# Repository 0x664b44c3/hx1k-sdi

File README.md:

# HX1k-SDI
An SDI encoder/serializer on Lattice iCE40 FPGAs

The iCE40 series of FPGAs is low cost and is supported by an opensource toolchain (though not currently used for this project)
The devices are low density and low speed and lack advanced features like SerDes or true LVDS-IO, though.

## Features of the serializer
 * fits multiple times into an 1k gates iCE40 FPGA
 * fpga-vendor agnostic, besides the specific instantiation of the SB_IO for DDR out
 * needs one PLL running at half the bitrate (or at full bitrate if your IO can run at 270MHz)
 * should be extendable to generate DVB-ASI (would need 8B/10B instead of SMPTE scrambler and NRZI)
 * accepts bt.656 video at 27MHz word rate

## Abstract
This project implements an SD-SDI serializer (aka transmitter) completely in fabric, requiring nothing but an unused PLL
that is used to generate a 135MHz from an externally supplied 27MHz sample clock (27MWords/s with CbYCrY 4:2:2 encoding, 
13.5MHz pixel clock).
Most of the logic operates at 27MHz with just the final multiplexer and a DDR-out buffer running at the full 135MHz.

## Features of the test board
 * iCE40HX1k FPGA
 * 27MHz crystal oscillator
 * 10bit bt.656 video port
 * TVP5151 video decoder to test analog to sdi conversion
   * alternatively/additionally an LMH1881 can be fitted
 * 1MByte (512kx16) of SRAM taht can hold one complete frame of interlaced PAL/NTCS
 * ATSAMD21G18 MCU for programming the FPGA config flash and configuring the TVP, can be omitted
 * 4-pin header for I2C 128x32 OLED display
 * FPGA config pins on pinheader to allow flashing the config without a MCU
 * switchmode regulator for the 3.3V rail, allows input voltages of 5 to 12V
* Current functionality in the FPGA demo project
   * Color bars generator
   * SDI pathological pattern generator
   * Analog to SDI converter
   * About half the FPGA is still free for additional functionality

## Scope
This project contains a complete eval board for SDI video generation on
iCE40-HX FPGAs. UP-series might work, too, but it's unclear if the IOB and Fabric are fast enaugh
(might test it on iCEBreaker at some point in time).

## Contents
This project consists of the following subfolders:
 * fpga: the FPGA design (VHDL, iCECube2 project)
 * hardware: The board design (eagle 6), schematic diagrams as PDF
 * firmware: Firmware for the ATSAMD21 MCU that is on the board as well
 * release: synthesized FPGA config, firmware image, gerbers etc

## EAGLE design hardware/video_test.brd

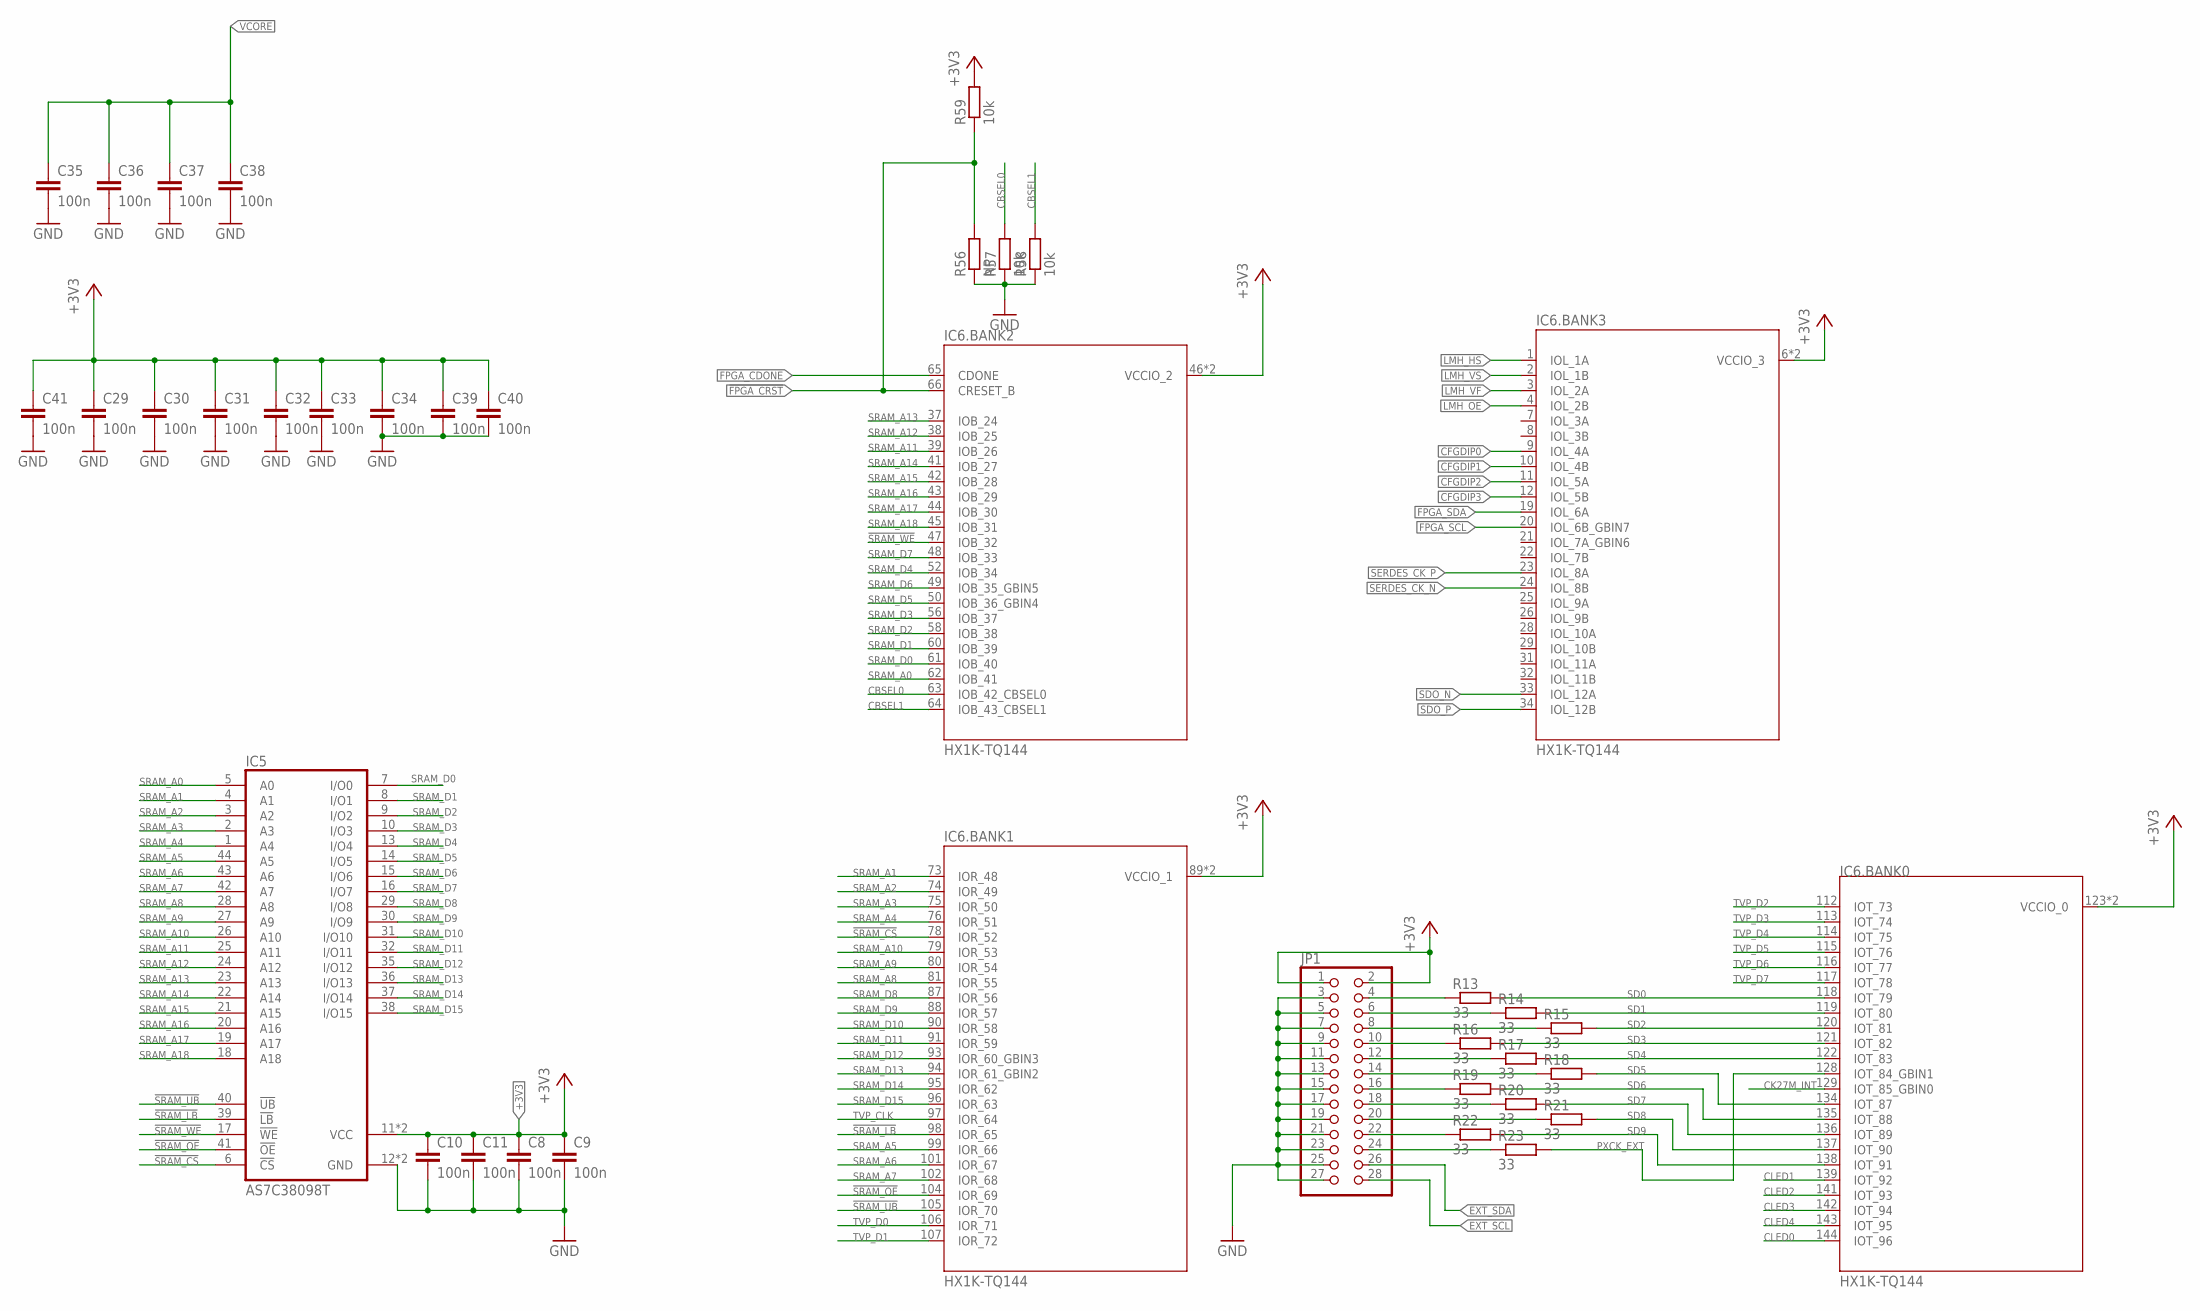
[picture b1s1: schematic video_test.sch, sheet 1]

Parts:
C8, C9: 100n; C0603
C10, C11, C29, C30, C31, C32, C33, C34, C35, C36, C37, C38, C39, C40, C41: 100n; C0402
IC5: AS7C38098T; TSOPII-Z44
IC6: HX1K-TQ144; QFP50P2200X2200X160-144N
JP1: PINHD-2X14; 2X14
R13, R14, R15, R16, R17, R18, R19, R20, R21, R22, R23: 33; R0603
R56: NP; R0402
R57, R58, R59: 10k; R0402

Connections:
!FPGA_CRST!: IC6.66 (CRESET_B), R56.2, R59.1; also elsewhere on the board
!SRAM_CS!: IC5.6 (!CS!), IC6.78 (IOR_52)
!SRAM_LB!: IC5.39 (!LB!), IC6.98 (IOR_65)
!SRAM_OE!: IC5.41 (!OE!), IC6.104 (IOR_69)
!SRAM_UB!: IC5.40 (!UB!), IC6.105 (IOR_70)
!SRAM_WE!: IC5.17 (!WE!), IC6.47 (IOB_32)
+3V3: C8.1, C9.1, C10.1, C11.1, C29.1, C30.1, C31.1, C32.1, C33.1, C34.1, C39.1, C40.1, C41.1, IC5.11 (VCC), IC5.33 (VCC), IC6.6 (VCCIO_3), IC6.30 (VCCIO_3), IC6.46 (VCCIO_2), IC6.57 (VCCIO_2), IC6.89 (VCCIO_1), IC6.100 (VCCIO_1), IC6.123 (VCCIO_0), IC6.133 (VCCIO_0), JP1.1, JP1.2, R59.2; also elsewhere on the board
CBSEL0: IC6.63 (IOB_42_CBSEL0), R57.2; also elsewhere on the board
CBSEL1: IC6.64 (IOB_43_CBSEL1), R58.2; also elsewhere on the board
CFGDIP0: IC6.9 (IOL_4A); also elsewhere on the board
CFGDIP1: IC6.10 (IOL_4B); also elsewhere on the board
CFGDIP2: IC6.11 (IOL_5A); also elsewhere on the board
CFGDIP3: IC6.12 (IOL_5B); also elsewhere on the board
CK27M_INT: IC6.129 (IOT_85_GBIN0); also elsewhere on the board
CLED0: IC6.144 (IOT_96); also elsewhere on the board
CLED1: IC6.139 (IOT_92); also elsewhere on the board
CLED2: IC6.141 (IOT_93); also elsewhere on the board
CLED3: IC6.142 (IOT_94); also elsewhere on the board
CLED4: IC6.143 (IOT_95); also elsewhere on the board
EXT_SCL: JP1.28; also elsewhere on the board
EXT_SDA: JP1.26; also elsewhere on the board
FPGA_CDONE: IC6.65 (CDONE); also elsewhere on the board
FPGA_SCL: IC6.20 (IOL_6B_GBIN7); also elsewhere on the board
FPGA_SDA: IC6.19 (IOL_6A); also elsewhere on the board
GND: C8.2, C9.2, C10.2, C11.2, C29.2, C30.2, C31.2, C32.2, C33.2, C34.2, C35.2, C36.2, C37.2, C38.2, C39.2, C40.2, C41.2, IC5.12 (GND), IC5.34 (GND), JP1.3, JP1.5, JP1.7, JP1.9, JP1.11, JP1.13, JP1.15, JP1.17, JP1.19, JP1.21, JP1.23, JP1.25, JP1.27, R56.1, R57.1, R58.1; also elsewhere on the board
LMH_HS: IC6.1 (IOL_1A); also elsewhere on the board
LMH_OE: IC6.4 (IOL_2B); also elsewhere on the board
LMH_VF: IC6.3 (IOL_2A); also elsewhere on the board
LMH_VS: IC6.2 (IOL_1B); also elsewhere on the board
unnamed: JP1.4, R13.1
unnamed: JP1.6, R14.1
unnamed: JP1.8, R15.1
unnamed: JP1.10, R16.1
unnamed: JP1.12, R17.1
unnamed: JP1.14, R18.1
unnamed: JP1.16, R19.1
unnamed: JP1.18, R20.1
unnamed: JP1.20, R21.1
unnamed: JP1.22, R22.1
unnamed: JP1.24, R23.1
PXCK_EXT: IC6.128 (IOT_84_GBIN1), R23.2
SD0: IC6.118 (IOT_79), R13.2
SD1: IC6.119 (IOT_80), R14.2
SD2: IC6.120 (IOT_81), R15.2
SD3: IC6.121 (IOT_82), R16.2
SD4: IC6.122 (IOT_83), R17.2
SD5: IC6.134 (IOT_87), R18.2
SD6: IC6.135 (IOT_88), R19.2
SD7: IC6.136 (IOT_89), R20.2
SD8: IC6.137 (IOT_90), R21.2
SD9: IC6.138 (IOT_91), R22.2
SDO_N: IC6.33 (IOL_12A); also elsewhere on the board
SDO_P: IC6.34 (IOL_12B); also elsewhere on the board
SERDES_CK_N: IC6.24 (IOL_8B); also elsewhere on the board
SERDES_CK_P: IC6.23 (IOL_8A); also elsewhere on the board
SRAM_A0: IC5.5 (A0), IC6.62 (IOB_41)
SRAM_A1: IC5.4 (A1), IC6.73 (IOR_48)
SRAM_A2: IC5.3 (A2), IC6.74 (IOR_49)
SRAM_A3: IC5.2 (A3), IC6.75 (IOR_50)
SRAM_A4: IC5.1 (A4), IC6.76 (IOR_51)
SRAM_A5: IC5.44 (A5), IC6.99 (IOR_66)
SRAM_A6: IC5.43 (A6), IC6.101 (IOR_67)
SRAM_A7: IC5.42 (A7), IC6.102 (IOR_68)
SRAM_A8: IC5.28 (A8), IC6.81 (IOR_55)
SRAM_A9: IC5.27 (A9), IC6.80 (IOR_54)
SRAM_A10: IC5.26 (A10), IC6.79 (IOR_53)
SRAM_A11: IC5.25 (A11), IC6.39 (IOB_26)
SRAM_A12: IC5.24 (A12), IC6.38 (IOB_25)
SRAM_A13: IC5.23 (A13), IC6.37 (IOB_24)
SRAM_A14: IC5.22 (A14), IC6.41 (IOB_27)
SRAM_A15: IC5.21 (A15), IC6.42 (IOB_28)
SRAM_A16: IC5.20 (A16), IC6.43 (IOB_29)
SRAM_A17: IC5.19 (A17), IC6.44 (IOB_30)
SRAM_A18: IC5.18 (A18), IC6.45 (IOB_31)
SRAM_D0: IC5.7 (I/O0), IC6.61 (IOB_40)
SRAM_D1: IC5.8 (I/O1), IC6.60 (IOB_39)
SRAM_D2: IC5.9 (I/O2), IC6.58 (IOB_38)
SRAM_D3: IC5.10 (I/O3), IC6.56 (IOB_37)
SRAM_D4: IC5.13 (I/O4), IC6.52 (IOB_34)
SRAM_D5: IC5.14 (I/O5), IC6.50 (IOB_36_GBIN4)
SRAM_D6: IC5.15 (I/O6), IC6.49 (IOB_35_GBIN5)
SRAM_D7: IC5.16 (I/O7), IC6.48 (IOB_33)
SRAM_D8: IC5.29 (I/O8), IC6.87 (IOR_56)
SRAM_D9: IC5.30 (I/O9), IC6.88 (IOR_57)
SRAM_D10: IC5.31 (I/O10), IC6.90 (IOR_58)
SRAM_D11: IC5.32 (I/O11), IC6.91 (IOR_59)
SRAM_D12: IC5.35 (I/O12), IC6.93 (IOR_60_GBIN3)
SRAM_D13: IC5.36 (I/O13), IC6.94 (IOR_61_GBIN2)
SRAM_D14: IC5.37 (I/O14), IC6.95 (IOR_62)
SRAM_D15: IC5.38 (I/O15), IC6.96 (IOR_63)
TVP_CLK: IC6.97 (IOR_64); also elsewhere on the board
TVP_D0: IC6.106 (IOR_71); also elsewhere on the board
TVP_D1: IC6.107 (IOR_72); also elsewhere on the board
TVP_D2: IC6.112 (IOT_73); also elsewhere on the board
TVP_D3: IC6.113 (IOT_74); also elsewhere on the board
TVP_D4: IC6.114 (IOT_75); also elsewhere on the board
TVP_D5: IC6.115 (IOT_76); also elsewhere on the board
TVP_D6: IC6.116 (IOT_77); also elsewhere on the board
TVP_D7: IC6.117 (IOT_78); also elsewhere on the board
VCORE: C35.1, C36.1, C37.1, C38.1; also elsewhere on the board
VPP_FAST: IC6.109 (VPP_FAST)

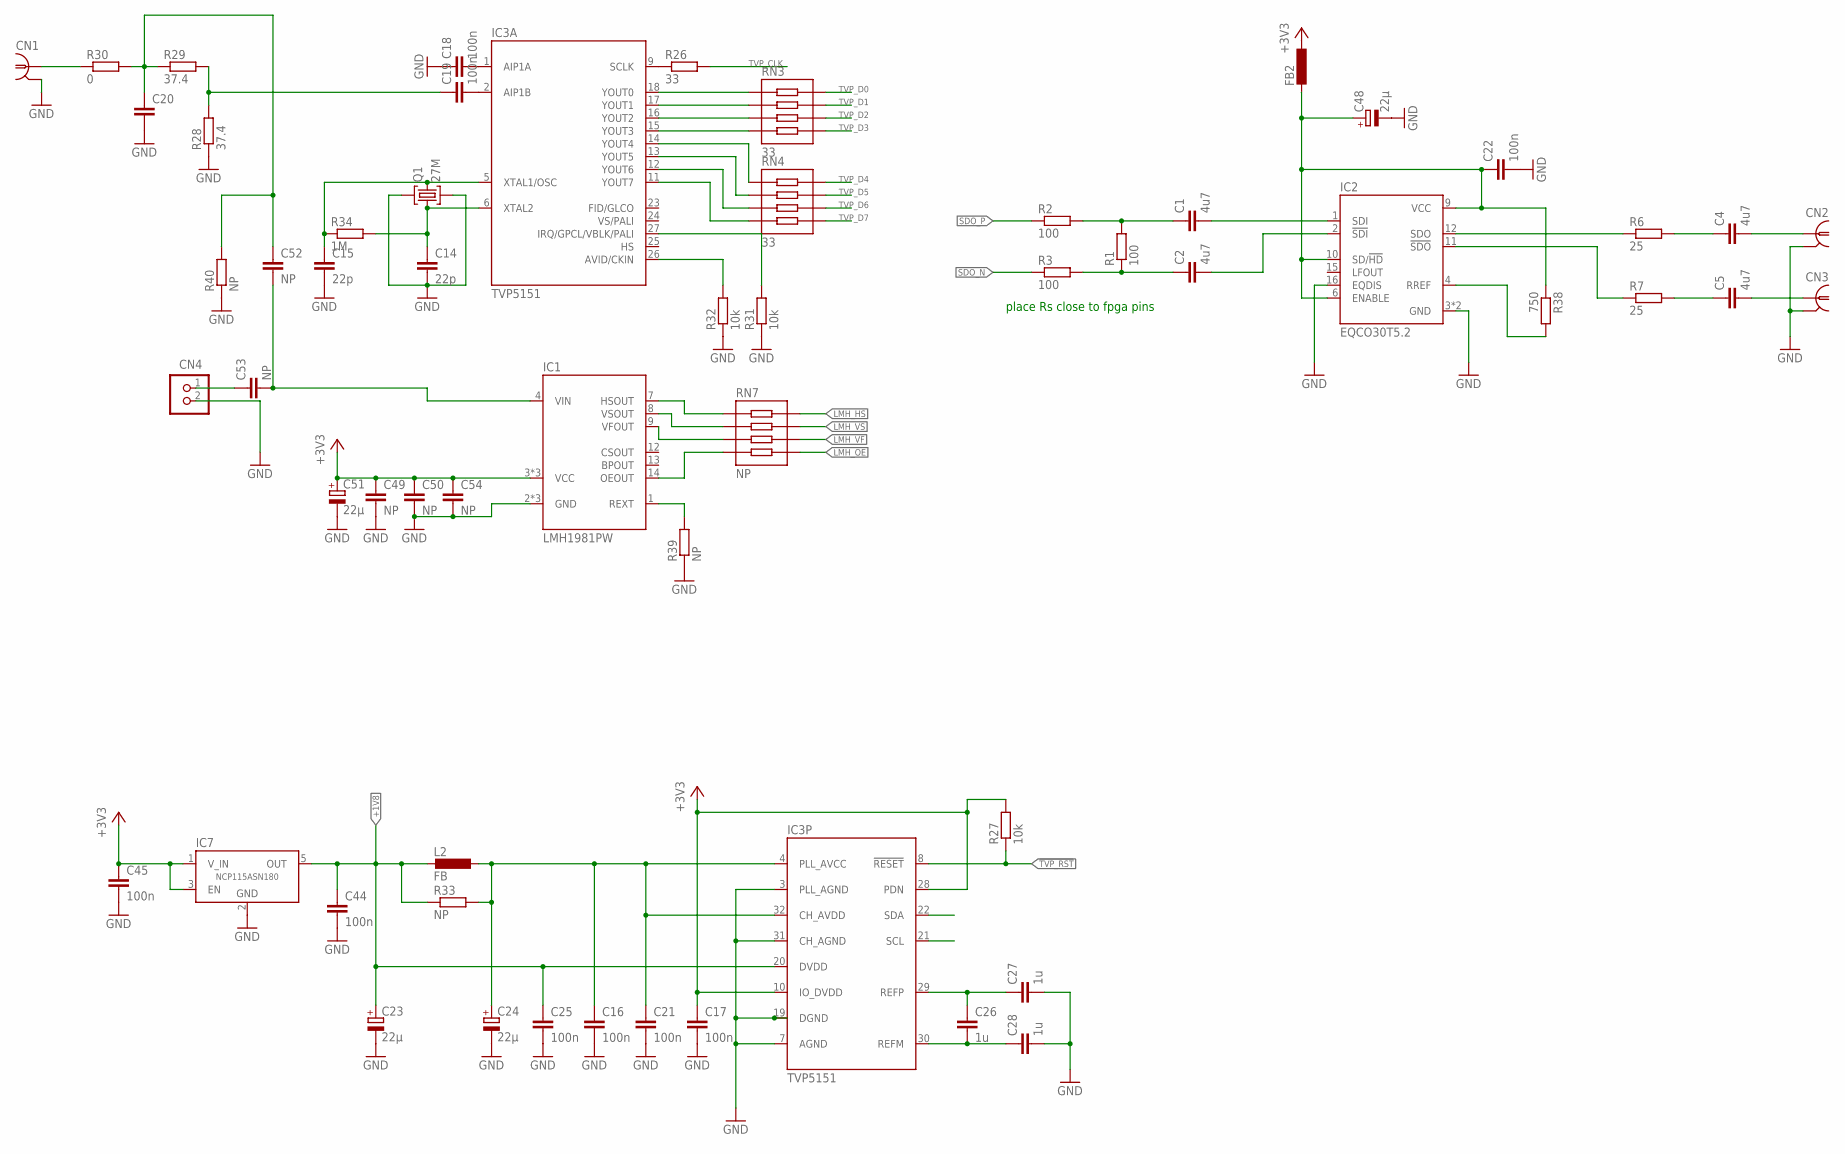
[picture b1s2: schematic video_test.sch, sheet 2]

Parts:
C1, C2, C4, C5: 4u7; C0603
C14, C15: 22p; C0603
C16, C17, C18, C19, C21, C22, C25: 100n; C0402
C20: C-EUC0603; C0603
C23, C24: 22µ; B/3528-21R
C26, C27, C28: 1u; C0603
C44, C45: 100n; C0603
C48, C51: 22µ; PANASONIC_B
C49, C50, C54: NP; C0402
C52, C53: NP; C0603
CN1, CN2, CN3: BU-BNC-RA; AMP_227161
CN4: JST-XH2; B2B-XH
FB2: L-EU_L0603; R0603
IC1: LMH1981PW; TSSOP14
IC2: EQCO30T5.2; QFN16_065
IC3: TVP5151; SPQFP32
IC7: NCP115ASN180; SOT23-5
L2: FB; R0805
Q1: 27M; MT
R1, R2, R3: 100; R0603
R6, R7: 25; R0603
R26: 33; R0603
R27, R31, R32: 10k; R0402
R28, R29: 37.4; R0603
R30: 0; R0603
R33, R39, R40: NP; R0603
R34: 1M; R0603
R38: 750; R0603
RN3, RN4: 33; CTS742C083
RN7: NP; CTS742C083

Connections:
!TVP_RST!: IC3.8 (!RESET!), R27.1
+1V8: C23.+, C25.1, C44.1, IC3.20 (DVDD), IC7.5 (OUT), L2.2, R33.1
+1V8_A: C16.1, C21.1, C24.+, IC3.4 (PLL_AVCC), IC3.32 (CH_AVDD), L2.1, R33.2
+3V3: C17.1, C45.1, C49.1, C50.1, C51.+, C54.1, FB2.1, IC1.3 (VCC), IC1.6 (VCC), IC1.11 (VCC), IC3.10 (IO_DVDD), IC3.28 (PDN), IC7.1 (V_IN), IC7.3 (EN), R27.2; also elsewhere on the board
GND: C14.2, C15.2, C16.2, C17.2, C18.1, C20.2, C21.2, C22.2, C23.-, C24.-, C25.2, C27.2, C28.2, C44.2, C45.2, C48.-, C49.2, C50.2, C51.-, C54.2, CN1.2 (GND), CN2.2 (GND), CN3.2 (GND), CN4.2, IC1.2 (GND), IC1.5 (GND), IC1.10 (GND), IC2.3 (GND), IC2.16 (EQDIS), IC2.TP (GND), IC3.3 (PLL_AGND), IC3.7 (AGND), IC3.19 (DGND), IC3.31 (CH_AGND), IC7.2 (GND), Q1.2 (G1), Q1.4 (G2), R28.1, R31.1, R32.1, R39.1, R40.1; also elsewhere on the board
LMH_HS: RN7.8 (B1); also elsewhere on the board
LMH_OE: RN7.5 (B4); also elsewhere on the board
LMH_VF: RN7.6 (B3); also elsewhere on the board
LMH_VS: RN7.7 (B2); also elsewhere on the board
unnamed: C1.2, IC2.1 (SDI)
unnamed: C2.2, IC2.2 (!SDI!)
unnamed: C2.1, R1.1, R3.2
unnamed: C1.1, R1.2, R2.2
unnamed: C4.1, R6.2
unnamed: C5.1, R7.2
unnamed: C4.2, CN2.1
unnamed: C5.2, CN3.1
unnamed: C22.1, C48.+, FB2.2, IC2.6 (ENABLE), IC2.9 (VCC), IC2.10 (SD/!HD!), R38.1
unnamed: IC2.4 (RREF), R38.2
unnamed: C15.1, IC3.5 (XTAL1/OSC), Q1.3 (2), R34.1
unnamed: C14.1, IC3.6 (XTAL2), Q1.1, R34.2
unnamed: C26.1, C27.1, IC3.29 (REFP)
unnamed: C26.2, C28.1, IC3.30 (REFM)
unnamed: C18.2, IC3.1 (AIP1A)
unnamed: IC3.11 (YOUT7), RN4.4 (A4)
unnamed: IC1.7 (HSOUT), RN7.1 (A1)
unnamed: IC3.9 (SCLK), R26.1
unnamed: IC3.12 (YOUT6), RN4.3 (A3)
unnamed: IC3.13 (YOUT5), RN4.2 (A2)
unnamed: IC3.14 (YOUT4), RN4.1 (A1)
unnamed: IC3.15 (YOUT3), RN3.4 (A4)
unnamed: IC3.16 (YOUT2), RN3.3 (A3)
unnamed: IC3.17 (YOUT1), RN3.2 (A2)
unnamed: IC3.18 (YOUT0), RN3.1 (A1)
unnamed: C19.2, IC3.2 (AIP1B)
unnamed: IC3.27 (IRQ/GPCL/VBLK/PALI), R31.2
unnamed: C19.1, R28.2, R29.2
unnamed: C20.1, C52.1, R29.1, R30.2, R40.2
unnamed: CN1.1, R30.1
unnamed: IC3.26 (AVID/CKIN), R32.2
unnamed: C52.2, C53.2, IC1.4 (VIN)
unnamed: C53.1, CN4.1
unnamed: IC1.8 (VSOUT), RN7.2 (A2)
unnamed: IC1.1 (REXT), R39.2
unnamed: IC1.9 (VFOUT), RN7.3 (A3)
unnamed: IC1.14 (OEOUT), RN7.4 (A4)
SCL: IC3.21 (SCL); also elsewhere on the board
SDA: IC3.22 (SDA); also elsewhere on the board
SDI_OUT_N: IC2.11 (!SDO!), R7.1
SDI_OUT_P: IC2.12 (SDO), R6.1
SDO_N: R3.1; also elsewhere on the board
SDO_P: R2.1; also elsewhere on the board
TVP_CLK: R26.2; also elsewhere on the board
TVP_D0: RN3.8 (B1); also elsewhere on the board
TVP_D1: RN3.7 (B2); also elsewhere on the board
TVP_D2: RN3.6 (B3); also elsewhere on the board
TVP_D3: RN3.5 (B4); also elsewhere on the board
TVP_D4: RN4.8 (B1); also elsewhere on the board
TVP_D5: RN4.7 (B2); also elsewhere on the board
TVP_D6: RN4.6 (B3); also elsewhere on the board
TVP_D7: RN4.5 (B4); also elsewhere on the board

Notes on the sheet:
place Rs close to fpga pins

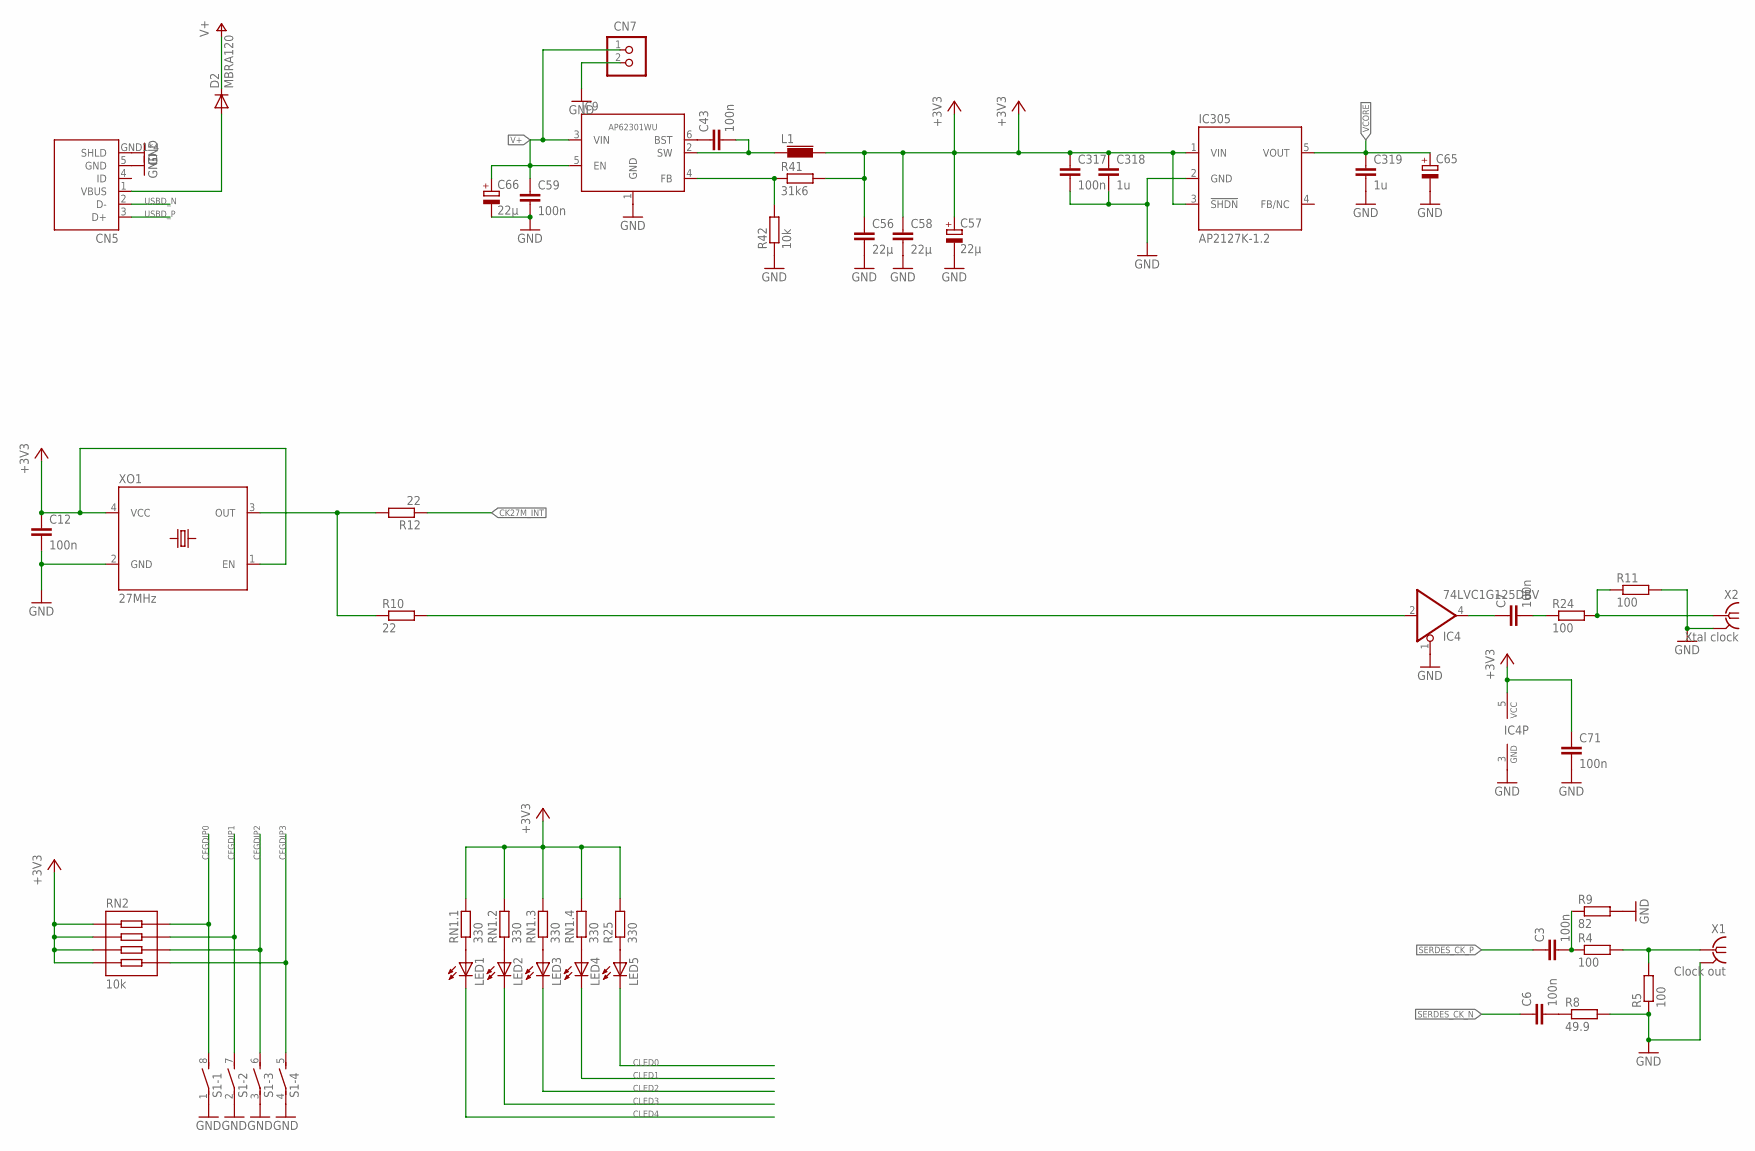
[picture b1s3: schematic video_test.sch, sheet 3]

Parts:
C3, C6, C7, C12, C43, C59, C71, C317: 100n; C0603
C56, C58: 22µ; C0805
C57: 22µ; PANASONIC_B
C65: CPOL-EUB/3528-21R; B/3528-21R
C66: 22µ; PANASONIC_C
C318, C319: 1u; C0603
CN5: USB-UJ2-MIBH-G; UJ2-MIBH-G-SMT
CN7: JST-XH2; B2B-XH
D2: MBRA120; SMA
IC4: 74LVC1G125DBV; SOT23-5
IC9: AP62301WU; SOT23-6L
IC305: AP2127K-1.2; SOT23-5
L1: L-TYA4020; TYA4020
LED1, LED2, LED3, LED4, LED5: LEDCHIP-LED0603; CHIP-LED0603
R4, R5, R11, R24: 100; R0603
R8: 49.9; R0603
R9: 82; R0603
R10, R12: 22; R0603
R25: 330; R0603
R41: 31k6; R0603
R42: 10k; R0603
RN1: 330; CTS742C083
RN2: 10k; CTS742C083
S1: DIP04S
X1: Clock out; BU-SMA-V
X2: Xtal clock; BU-SMA-V
XO1: 27MHz; ECS-2333

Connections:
+3V3: C12.1, C56.1, C57.+, C58.1, C71.1, C317.1, C318.1, IC4.5 (VCC), IC305.1 (VIN), IC305.3 (!SHDN!), L1.2, R25.2, R41.2, RN1.5 (2), RN1.6 (2), RN1.7 (2), RN1.8 (2), RN2.1 (A1), RN2.2 (A2), RN2.3 (A3), RN2.4 (A4), XO1.1 (EN), XO1.4 (VCC); also elsewhere on the board
CFGDIP0: RN2.8 (B1), S1.8 (2); also elsewhere on the board
CFGDIP1: RN2.7 (B2), S1.7 (2); also elsewhere on the board
CFGDIP2: RN2.6 (B3), S1.6 (2); also elsewhere on the board
CFGDIP3: RN2.5 (B4), S1.5 (2); also elsewhere on the board
CK27M_INT: R12.1; also elsewhere on the board
CLED0: LED5.C; also elsewhere on the board
CLED1: LED4.C; also elsewhere on the board
CLED2: LED3.C; also elsewhere on the board
CLED3: LED2.C; also elsewhere on the board
CLED4: LED1.C; also elsewhere on the board
GND: C12.2, C56.2, C57.-, C58.2, C59.2, C65.-, C66.-, C71.2, C317.2, C318.2, C319.2, CN5.5 (GND), CN5.GND1 (SHLD), CN5.GND2 (SHLD), CN5.GND3 (SHLD), CN5.GND4 (SHLD), CN7.2, IC4.1 (OE), IC4.3 (GND), IC9.1 (GND), IC305.2 (GND), R5.1, R8.2, R9.2, R11.2, R42.1, S1.1, S1.2 (1), S1.3 (1), S1.4 (1), X1.2 (GND), X1.3 (GND), X1.4 (GND), X1.5 (GND), X2.2 (GND), X2.3 (GND), X2.4 (GND), X2.5 (GND), XO1.2 (GND); also elsewhere on the board
unnamed: R4.2, R5.2, X1.1
unnamed: C6.2, R8.1
unnamed: C3.2, R4.1, R9.1
unnamed: R11.1, R24.2, X2.1
unnamed: IC4.2 (I), R10.2
unnamed: R10.1, R12.2, XO1.3 (OUT)
unnamed: C7.1, IC4.4 (O)
unnamed: C7.2, R24.1
unnamed: C43.2, IC9.2 (SW), L1.1
unnamed: LED1.A, RN1.1
unnamed: LED2.A, RN1.2 (1)
unnamed: LED3.A, RN1.3 (1)
unnamed: LED4.A, RN1.4 (1)
unnamed: LED5.A, R25.1
unnamed: C43.1, IC9.6 (BST)
unnamed: IC9.4 (FB), R41.1, R42.2
unnamed: CN5.1 (VBUS), D2.A
SERDES_CK_N: C6.1; also elsewhere on the board
SERDES_CK_P: C3.1; also elsewhere on the board
USBD_N: CN5.2 (D-); also elsewhere on the board
USBD_P: CN5.3 (D+); also elsewhere on the board
V+: C59.1, C66.+, CN7.1, D2.C, IC9.3 (VIN), IC9.5 (EN)
VCORE: C65.+, C319.1, IC305.5 (VOUT); also elsewhere on the board

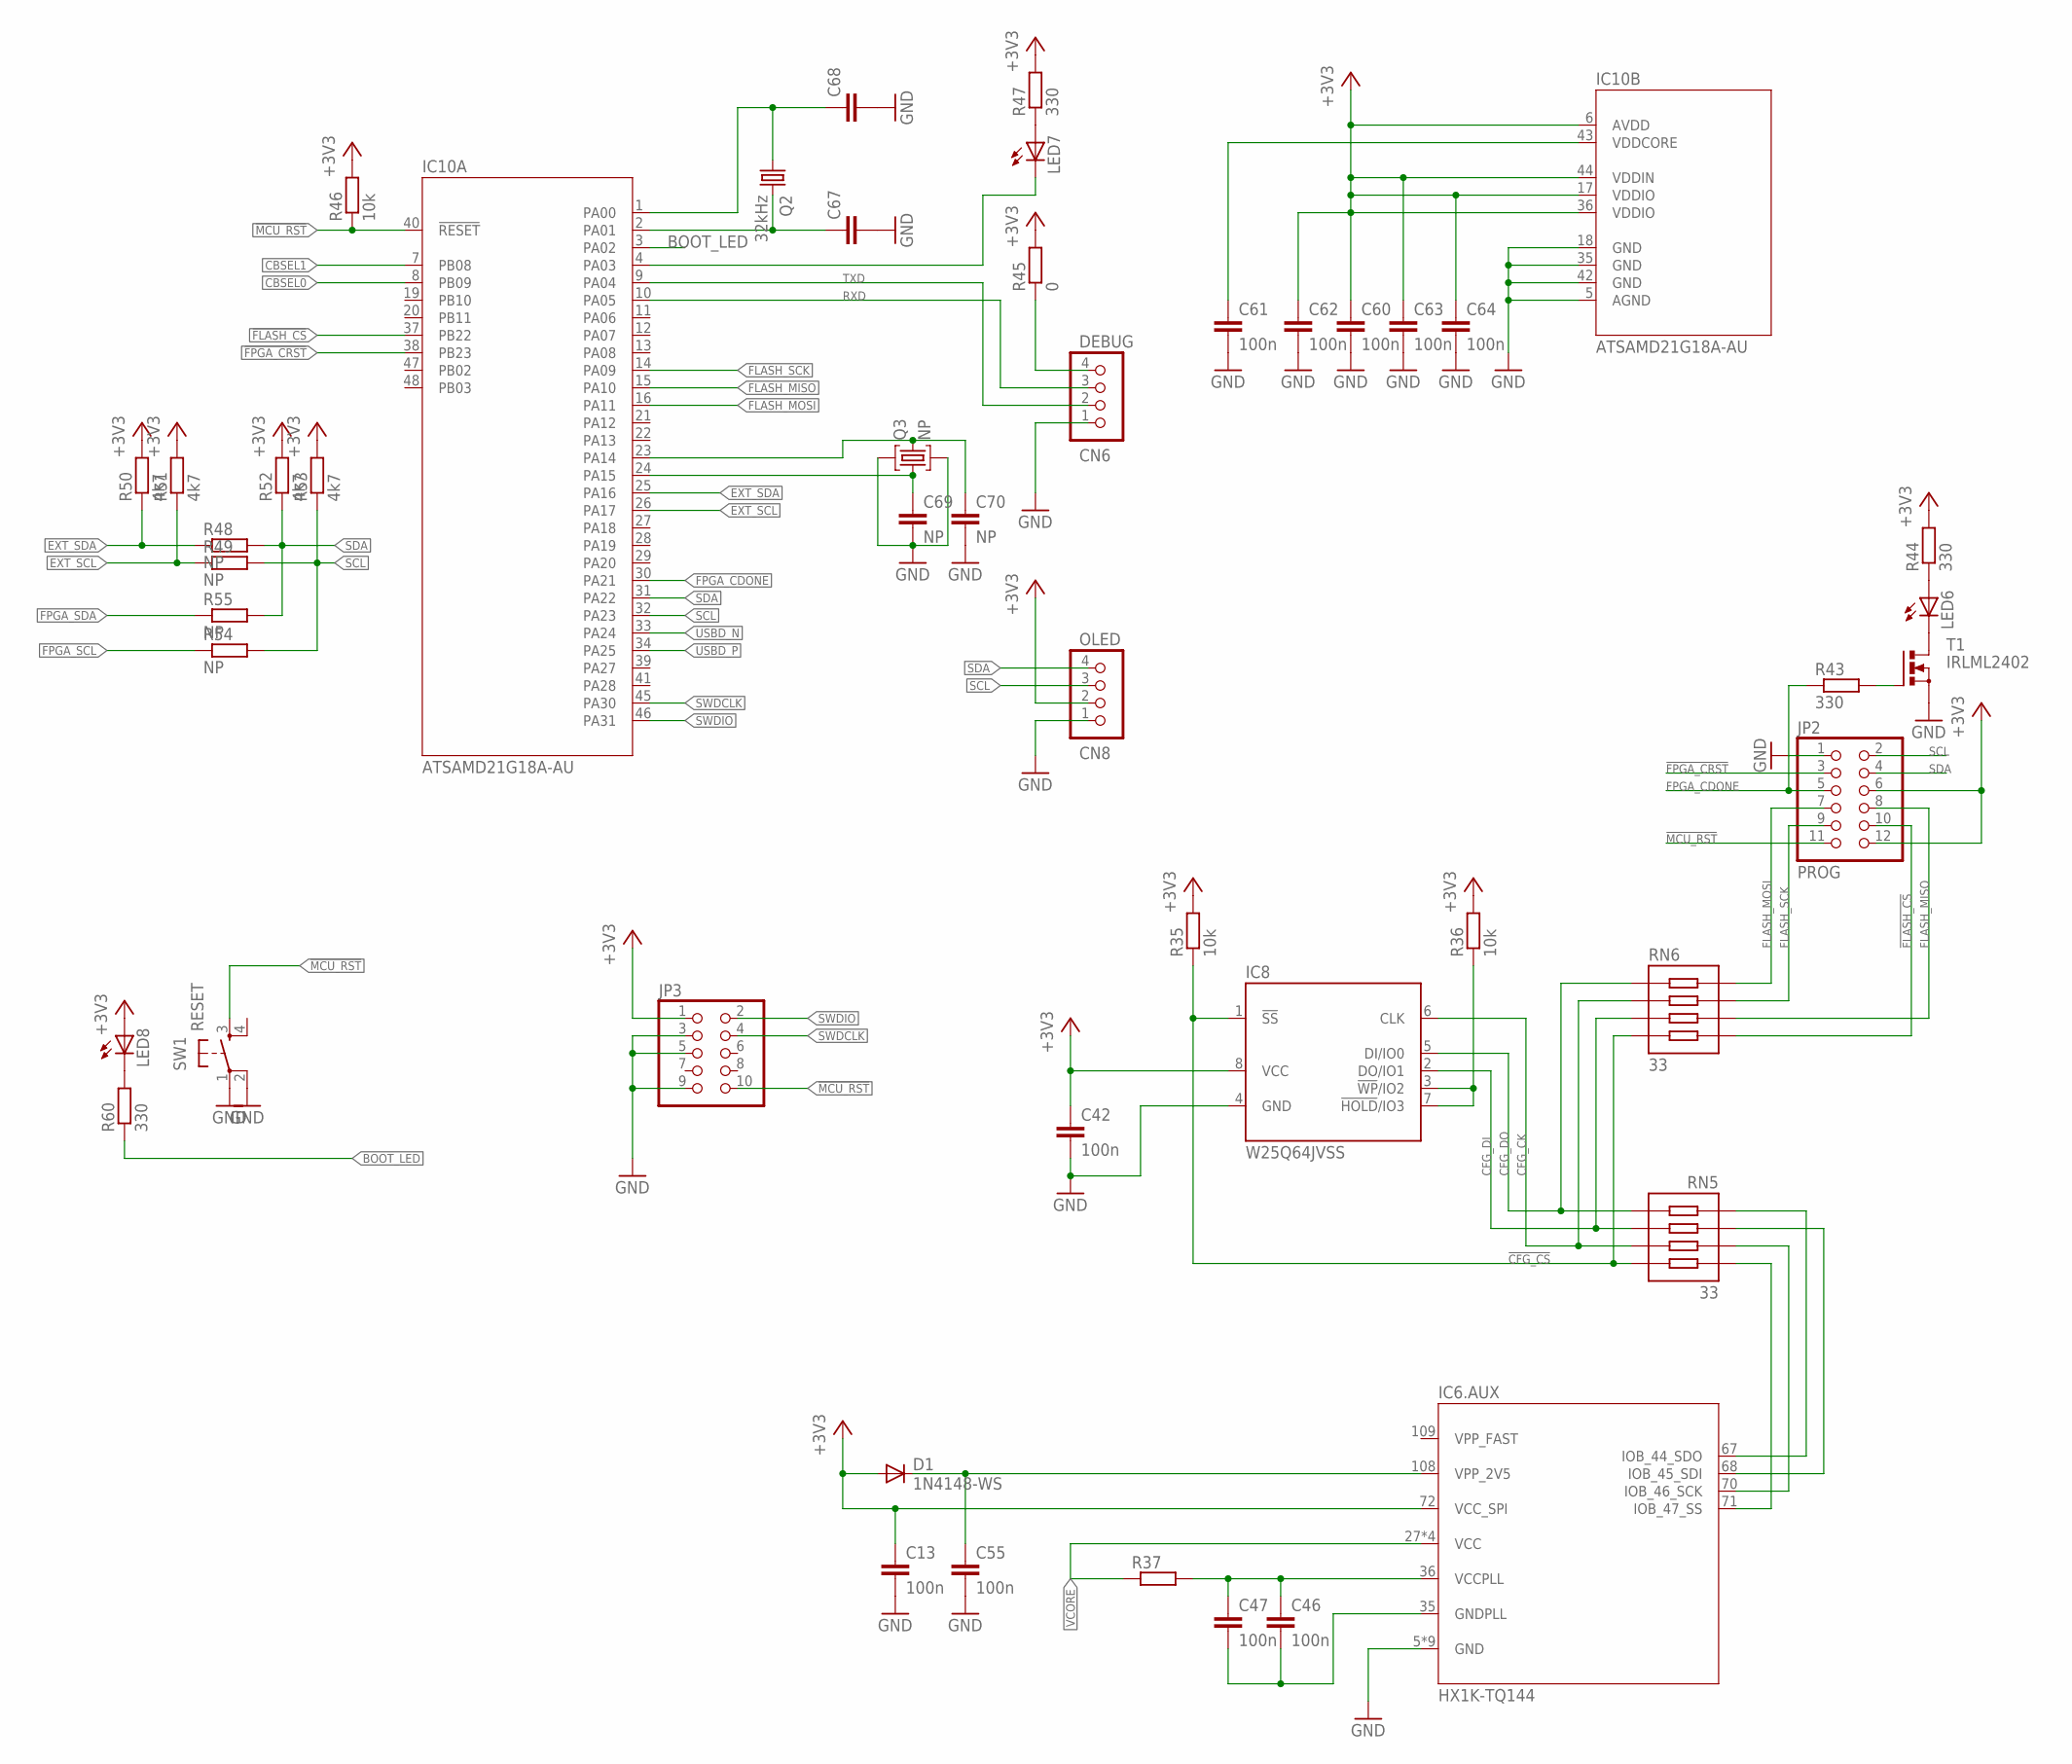
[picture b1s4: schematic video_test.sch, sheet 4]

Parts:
C13, C46, C55, C60, C61, C62, C63, C64: 100n; C0402
C42, C47: 100n; C0603
C67, C68: C-EUC0402; C0402
C69, C70: NP; C0603
CN6: DEBUG; SL-254-RH-4
CN8: OLED; SL-254-RH-4
D1: 1N4148-WS; SOD323
IC6: HX1K-TQ144; QFP50P2200X2200X160-144N
IC8: W25Q64JVSS; SO-08M
IC10: ATSAMD21G18A-AU; TQFP48_7X7MC_MCH
JP2: PROG; 2X06
JP3: PINHD-2X5-127; SL127-2X5
LED6, LED7, LED8: LEDCHIP-LED0603; CHIP-LED0603
Q2: 32kHz; IQXC-25
Q3: NP; MT
R35, R36, R46: 10k; R0603
R37: R-EU_R0603; R0603
R43, R44, R47, R60: 330; R0603
R45: 0; R0603
R48, R49: NP; R0603
R50, R51, R52, R53: 4k7; R0603
R54, R55: NP; R0402
RN5, RN6: 33; CTS742C083
SW1: RESET; PTS526
T1: IRLML2402; SOT23

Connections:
!CFG_CS!: IC8.1 (!SS!), R35.1, RN5.5 (B4), RN6.4 (A4)
!FLASH_CS!: IC10.37 (PB22), JP2.10, RN6.5 (B4)
!FPGA_CRST!: IC10.38 (PB23), JP2.3; also elsewhere on the board
!MCU_RST!: IC10.40 (!RESET), JP2.11, JP3.10, R46.1, SW1.3 (S)
+3V3: C13.1, C42.1, C60.1, C62.1, C63.1, C64.1, CN8.2, D1.A, IC6.72 (VCC_SPI), IC8.8 (VCC), IC10.6 (AVDD), IC10.17 (VDDIO), IC10.36 (VDDIO), IC10.44 (VDDIN), JP2.6, JP2.12, JP3.1, LED8.A, R35.2, R36.2, R44.2, R45.2, R46.2, R47.2, R50.2, R51.2, R52.2, R53.2; also elsewhere on the board
BOOT_LED: IC10.3 (PA02), R60.1
CBSEL0: IC10.8 (PB09); also elsewhere on the board
CBSEL1: IC10.7 (PB08); also elsewhere on the board
CFG_CK: IC8.6 (CLK), RN5.6 (B3), RN6.2 (A2)
CFG_DI: IC8.2 (DO/IO1), RN5.7 (B2), RN6.3 (A3)
CFG_DO: IC8.5 (DI/IO0), RN5.8 (B1), RN6.1 (A1)
EXT_SCL: IC10.26 (PA17), R49.1, R51.1; also elsewhere on the board
EXT_SDA: IC10.25 (PA16), R48.1, R50.1; also elsewhere on the board
FLASH_MISO: IC10.15 (PA10), JP2.8, RN6.6 (B3)
FLASH_MOSI: IC10.16 (PA11), JP2.7, RN6.8 (B1)
FLASH_SCK: IC10.14 (PA09), JP2.9, RN6.7 (B2)
FPGA_CDONE: IC10.30 (PA21), JP2.5, R43.1; also elsewhere on the board
FPGA_CS: IC6.71 (IOB_47_SS), RN5.4 (A4)
FPGA_SCK: IC6.70 (IOB_46_SCK), RN5.3 (A3)
FPGA_SCL: R54.1; also elsewhere on the board
FPGA_SDA: R55.1; also elsewhere on the board
FPGA_SDI: IC6.68 (IOB_45_SDI), RN5.2 (A2)
FPGA_SDO: IC6.67 (IOB_44_SDO), RN5.1 (A1)
GND: C13.2, C42.2, C55.2, C60.2, C61.2, C62.2, C63.2, C64.2, C67.2, C68.2, C69.2, C70.2, CN6.1, CN8.1, IC6.5 (GND), IC6.13 (GND), IC6.14 (GND), IC6.59 (GND), IC6.69 (GND), IC6.86 (GND), IC6.103 (GND), IC6.132 (GND), IC6.140 (GND), IC8.4 (GND), IC10.5 (AGND), IC10.18 (GND), IC10.35 (GND), IC10.42 (GND), JP2.1, JP3.3, JP3.5, JP3.9, Q3.2 (G1), Q3.4 (G2), SW1.1, SW1.2 (P1), T1.2 (S); also elsewhere on the board
GNDPLL: C46.2, C47.2, IC6.35 (GNDPLL)
unnamed: C55.1, D1.K (C), IC6.108 (VPP_2V5)
unnamed: IC8.3 (!WP!/IO2), IC8.7 (!HOLD!/IO3), R36.1
unnamed: LED6.C, T1.3 (D)
unnamed: R43.2, T1.1 (G)
unnamed: LED6.A, R44.1
unnamed: C67.1, IC10.2 (PA01), Q2.2
unnamed: C61.1, IC10.43 (VDDCORE)
unnamed: CN6.4, R45.1
unnamed: C68.1, IC10.1 (PA00), Q2.1
unnamed: C69.1, IC10.24 (PA15), Q3.1
unnamed: C70.1, IC10.23 (PA14), Q3.3 (2)
unnamed: LED7.A, R47.1
unnamed: IC10.4 (PA03), LED7.C
unnamed: LED8.C, R60.2
RXD: CN6.3, IC10.10 (PA05)
SCL: CN8.3, IC10.32 (PA23), JP2.2, R49.2, R53.1, R54.2; also elsewhere on the board
SDA: CN8.4, IC10.31 (PA22), JP2.4, R48.2, R52.1, R55.2; also elsewhere on the board
SWDCLK: IC10.45 (PA30), JP3.4
SWDIO: IC10.46 (PA31), JP3.2
TXD: CN6.2, IC10.9 (PA04)
USBD_N: IC10.33 (PA24); also elsewhere on the board
USBD_P: IC10.34 (PA25); also elsewhere on the board
VCCPLL: C46.1, C47.1, IC6.36 (VCCPLL), R37.2
VCORE: IC6.27 (VCC), IC6.51 (VCC), IC6.92 (VCC), IC6.111 (VCC), R37.1; also elsewhere on the board
VPP_FAST: IC6.109 (VPP_FAST)

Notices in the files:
parts and their libraries:
COPYRIGHT: Copyright (C) 2018 Accelerated Designs. All rights reserved
